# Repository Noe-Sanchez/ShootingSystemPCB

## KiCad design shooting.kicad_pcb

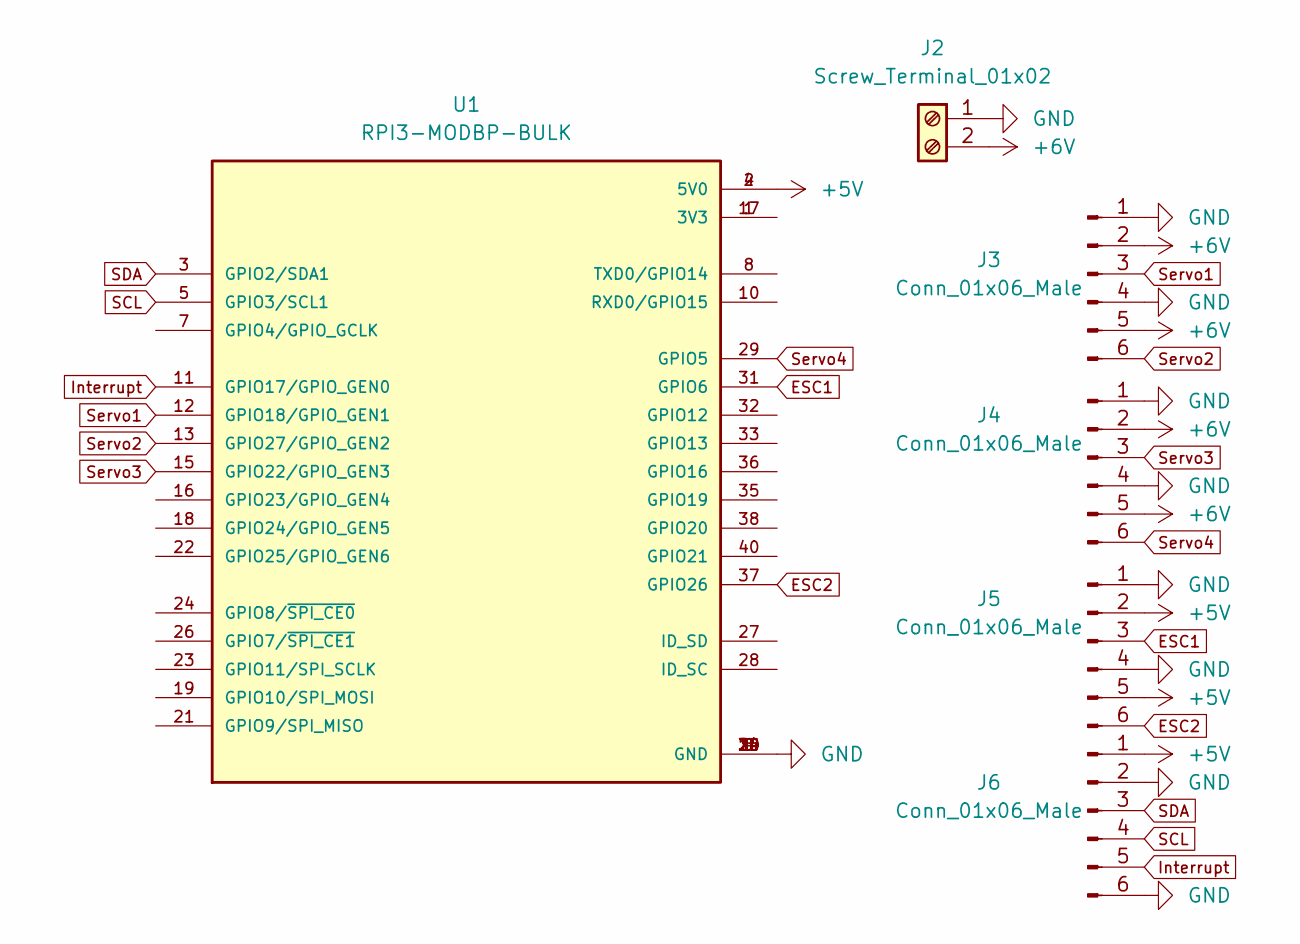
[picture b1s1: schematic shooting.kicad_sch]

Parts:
J2: Screw_Terminal_01x02; TerminalBlock_bornier-2_P5.08mm
J3, J4, J5, J6: Conn_01x06_Male; JST_XA_S06B-XASK-1_1x06_P2.50mm_Horizontal
U1: RPI3-MODBP-BULK; MODULE_RPI3-MODBP-BULK; PARTREV 1.0

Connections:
+5V: J5.2, J5.5, J6.1, U1.2 (5V0), U1.4 (5V0)
+6V: J2.2, J3.2, J3.5, J4.2, J4.5
ESC1: J5.3, U1.31 (GPIO6)
ESC2: J5.6, U1.37 (GPIO26)
GND: J2.1, J3.1, J3.4, J4.1, J4.4, J5.1, J5.4, J6.2, J6.6, U1.6 (GND), U1.9 (GND), U1.14 (GND), U1.20 (GND), U1.25 (GND), U1.30 (GND), U1.34 (GND), U1.39 (GND)
Interrupt: J6.5, U1.11 (GPIO17/GPIO_GEN0)
unnamed: U1.1 (3V3), U1.17 (3V3)
SCL: J6.4, U1.5 (GPIO3/SCL1)
SDA: J6.3, U1.3 (GPIO2/SDA1)
Servo1: J3.3, U1.12 (GPIO18/GPIO_GEN1)
Servo2: J3.6, U1.13 (GPIO27/GPIO_GEN2)
Servo3: J4.3, U1.15 (GPIO22/GPIO_GEN3)
Servo4: J4.6, U1.29 (GPIO5)

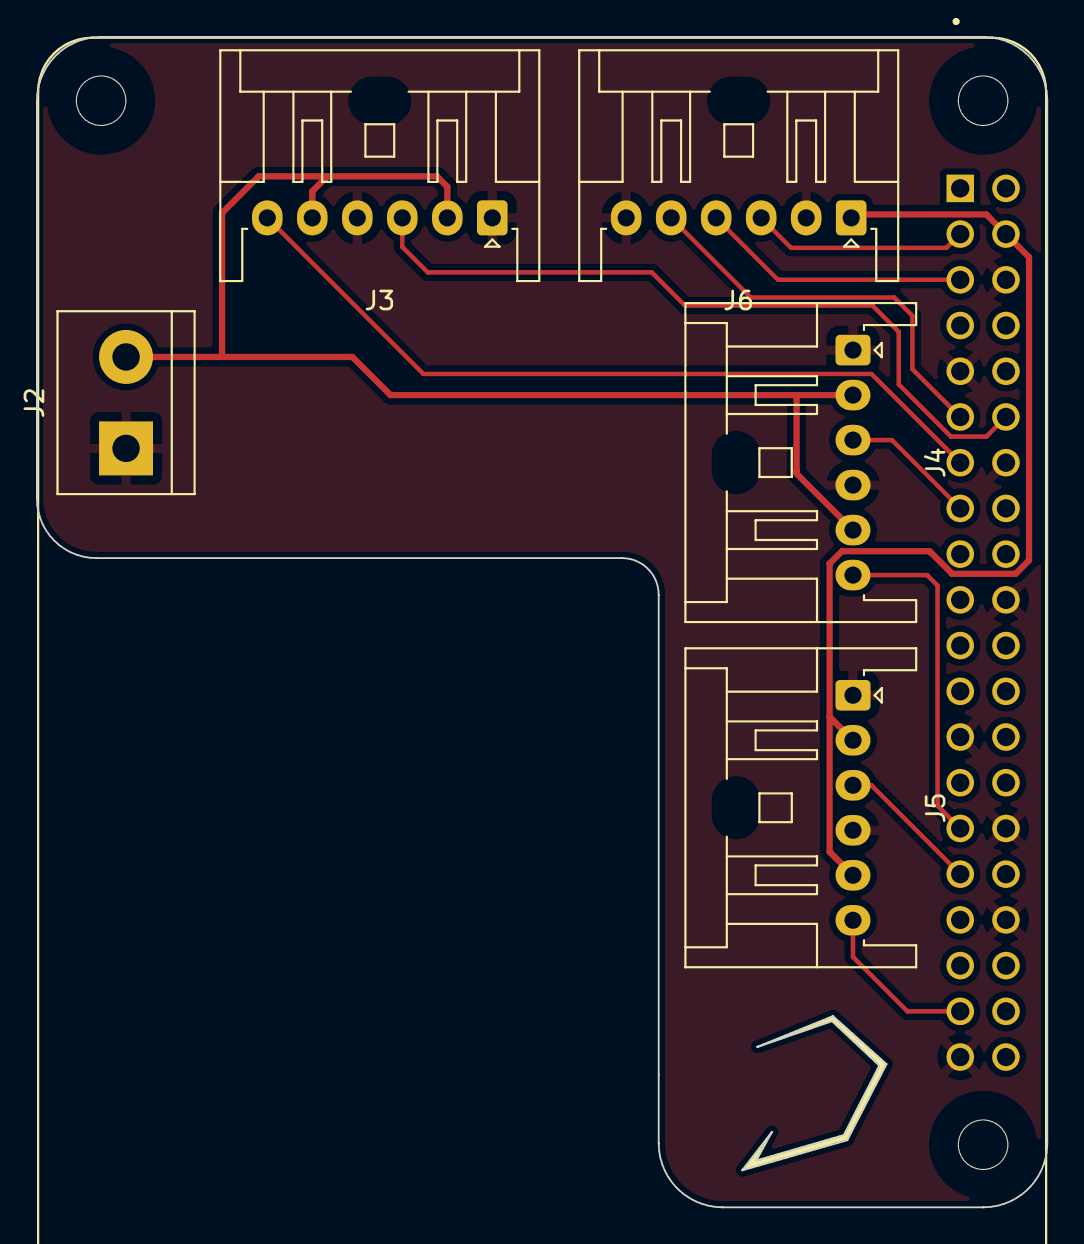
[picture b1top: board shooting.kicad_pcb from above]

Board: 2 copper layers, 56.1 x 65.0 mm, 6 parts (0 on the bottom side), 13 nets.

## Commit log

2023-02-22 Rev0.1
